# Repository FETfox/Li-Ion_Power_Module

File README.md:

## Status

  **RevA** In development (schematic complete, layout pending)

## Key Components

| Function | IC | Notes |
|----------|----|----|
| Charger | BQ24074 | USB100/500 + ILIM modes |
| Protection | BQ29728 | OCP/OVP/UVP |
| Fuel Gauge | BQ27427 | Coulomb counter |
| Buck-Boost | TPS63020 | ~1.8-5.5V input, 3.3V/5V output |
| MCU (Smart) | ATtiny3217 | CAN interface logic |
| CAN Controller | MCP2515 | SPI interface |
| CAN Transceiver | SN65HVD230 | ISO11898-2 compliant |

## Usage

Battery powered 5w power supply for projects that use 3v3 or 5v.
The smart version tracks system status and communicates over CAN bus.

## Known Issues / TODOs

- [ ] PCB layout and thermal analysis
- [ ] Publish assembly guide and test procedure

## License

CC0

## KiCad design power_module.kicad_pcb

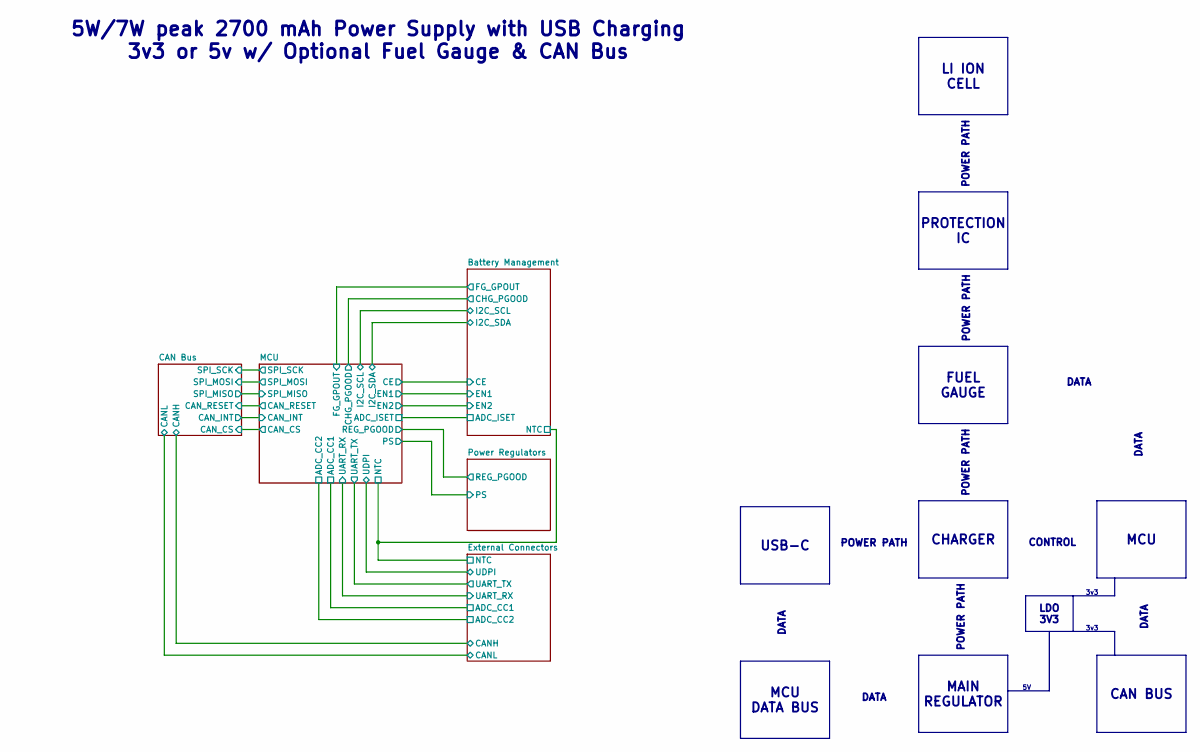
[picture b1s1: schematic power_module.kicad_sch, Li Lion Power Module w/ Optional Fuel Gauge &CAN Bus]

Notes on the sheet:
3v3
5W/7W peak 2700 mAh Power Supply with USB Charging 3v3 or 5v w/ Optional Fuel Gauge & CAN Bus
LDO 3V3
FUEL GAUGE
MCU DATA BUS
DATA
CHARGER
POWER PATH
USB-C
CAN BUS
MAIN REGULATOR
PROTECTION IC
LI ION CELL
MCU
CONTROL

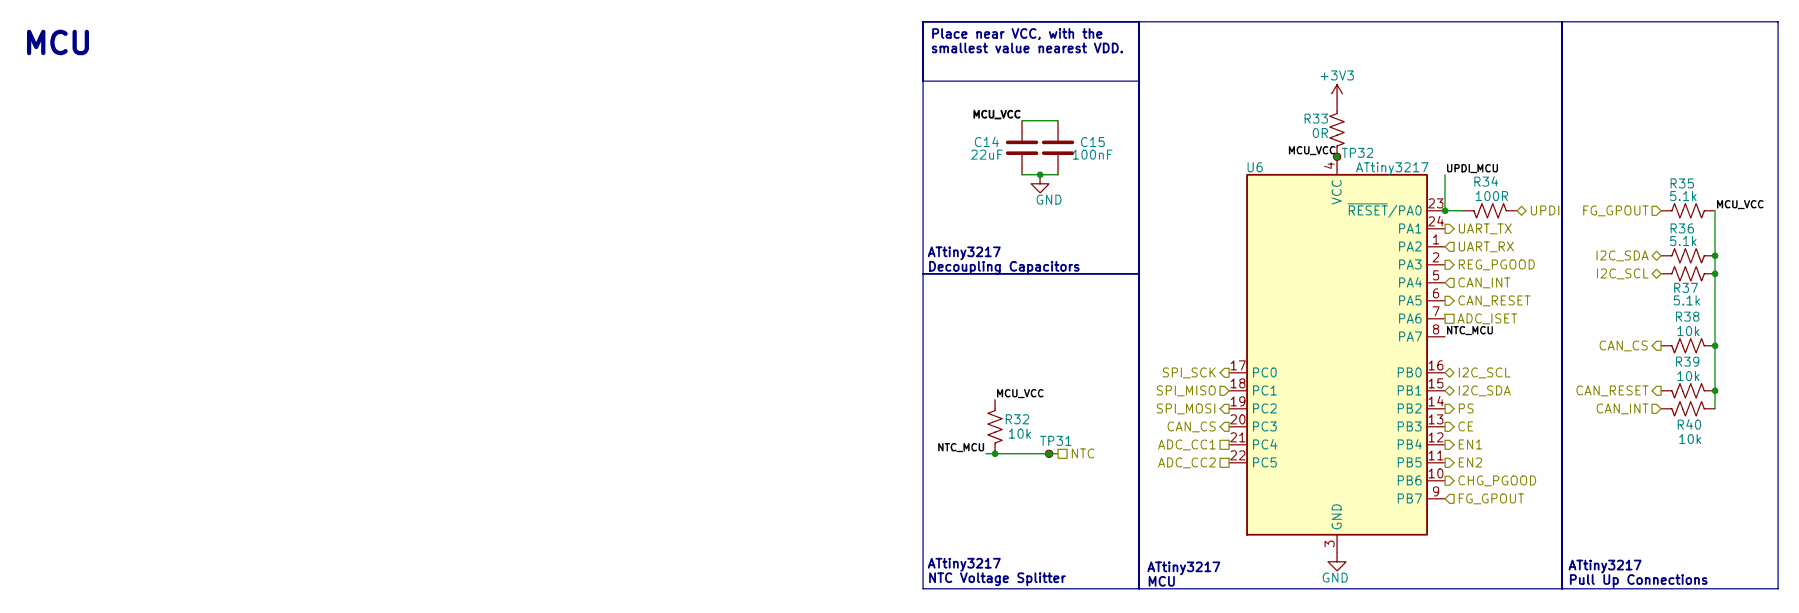
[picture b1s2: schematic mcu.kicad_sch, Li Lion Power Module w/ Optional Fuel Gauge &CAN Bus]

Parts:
C14: 22uF; C_0805_2012Metric; LCSC# C77074
C15: 100nF; C_0603_1608Metric; LCSC# C14663
R32, R38, R39, R40: 10k; R_0603_1608Metric; MFR# RC0603FR-0710KL; LCSC# C98220
R33: 0R; R_0805_2012Metric; LCSC# C54921246
R34: 100R; R_0603_1608Metric; MFR# RC0603FR-07100RL; LCSC# C105588
R35, R36, R37: 5.1k; R_0603_1608Metric; MFR# RC0603FR-075K1L; LCSC# C105580
TP31: NTC; TestPoint_Pad_D1.0mm
TP32: MCU_VCC; TestPoint_Pad_D1.0mm
U6: ATtiny3217; QFN-24-1EP_4x4mm_P0.5mm_EP2.6x2.6mm; LCSC# C15193

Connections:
+3V3: R33.1; also elsewhere on the board
/Battery Management/ADC_ISET: U6.7 (PA6); also elsewhere on the board
/Battery Management/CE: U6.13 (PB3); also elsewhere on the board
/Battery Management/CHG_EN1: U6.12 (PB4); also elsewhere on the board
/Battery Management/CHG_EN2: U6.11 (PB5); also elsewhere on the board
/Battery Management/CHG_PGOOD: U6.10 (PB6); also elsewhere on the board
/Battery Management/FG_GPOUT: R35.1, U6.9 (PB7); also elsewhere on the board
/Battery Management/I2C_SCL: R37.2, U6.16 (PB0); also elsewhere on the board
/Battery Management/I2C_SDA: R36.1, U6.15 (PB1); also elsewhere on the board
/CAN Bus/CAN_CS: R38.2, U6.20 (PC3); also elsewhere on the board
/CAN Bus/CAN_INT: R40.1, U6.5 (PA4); also elsewhere on the board
/CAN Bus/CAN_RESET: R39.2, U6.6 (PA5); also elsewhere on the board
/CAN Bus/SPI_MISO: U6.18 (PC1); also elsewhere on the board
/CAN Bus/SPI_MOSI: U6.19 (PC2); also elsewhere on the board
/CAN Bus/SPI_SCK: U6.17 (PC0); also elsewhere on the board
/External Connectors/ADC_CC1: U6.21 (PC4); also elsewhere on the board
/External Connectors/ADC_CC2: U6.22 (PC5); also elsewhere on the board
/External Connectors/UART_RX: U6.1 (PA2); also elsewhere on the board
/External Connectors/UART_TX: U6.24 (PA1); also elsewhere on the board
/MCU/MCU_VCC: C14.2, C15.2, R32.2, R33.2, R35.2, R36.2, R37.1, R38.1, R39.1, R40.2, TP32.1 (1_1), U6.4 (VCC)
/MCU/NTC_MCU: R32.1, TP31.1 (1_1), U6.8 (PA7); also elsewhere on the board
/MCU/PS: U6.14 (PB2); also elsewhere on the board
/MCU/UPDI: R34.2
/MCU/UPDI_MCU: R34.1, U6.23 (~RESET/PA0)
/Power Regulators/REG_PGOOD: U6.2 (PA3); also elsewhere on the board
GND: C14.1, C15.1, U6.3 (GND), U6.25 (GND); also elsewhere on the board

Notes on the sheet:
ATtiny3217 Pull Up Connections
ATtiny3217 MCU
MCU
ATtiny3217 NTC Voltage Splitter
ATtiny3217 Decoupling Capacitors
Place near VCC, with the smallest value nearest VDD.

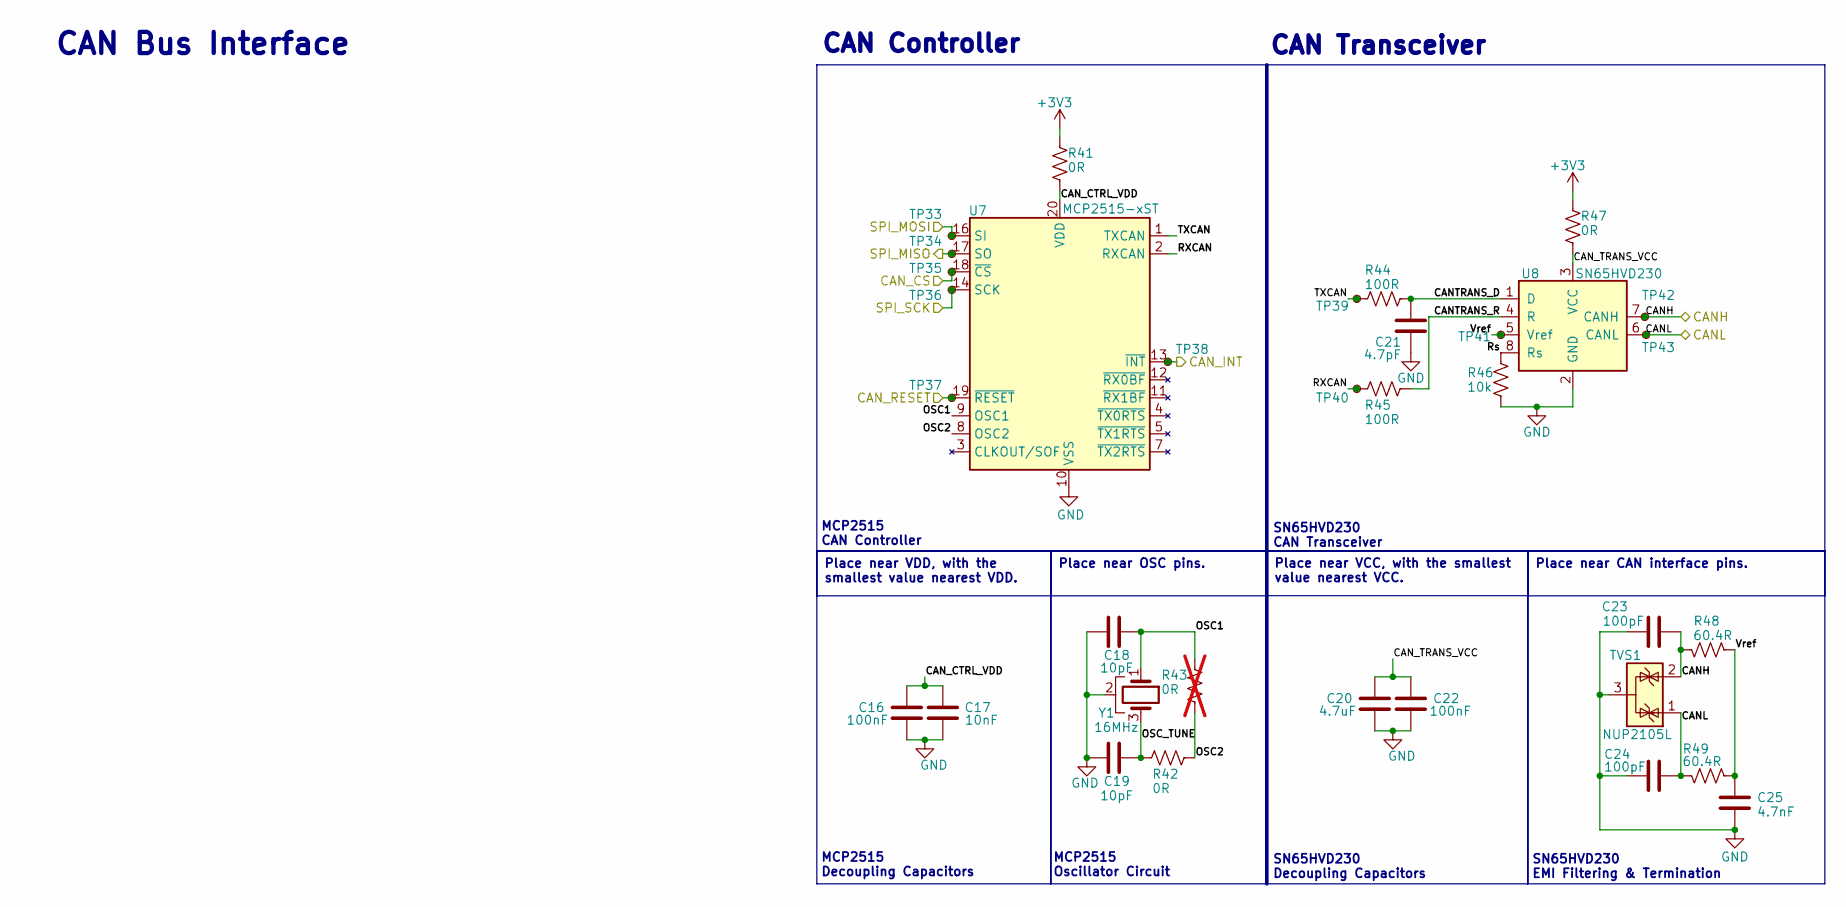
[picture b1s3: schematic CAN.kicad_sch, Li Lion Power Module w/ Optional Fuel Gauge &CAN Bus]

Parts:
C16, C22: 100nF; C_0603_1608Metric; LCSC# C14663
C17: 10nF; C_0603_1608Metric; LCSC# C100042
C18, C19: 10pF; C_0603_1608Metric; LCSC# C106245
C20: 4.7uF; C_0805_2012Metric; LCSC# C96454
C21: 4.7pF; C_0603_1608Metric; LCSC# C1669
C23, C24: 100pF; C_0603_1608Metric; LCSC# C14858
C25: 4.7nF; C_0603_1608Metric; LCSC# C16194364
R41, R42, R47: 0R; R_0805_2012Metric; LCSC# C54921246
R43: 0R; R_0805_2012Metric; LCSC# C54921246; not fitted
R44, R45: 100R; R_0603_1608Metric; LCSC# C105588
R46: 10k; R_0603_1608Metric; LCSC# C98220
R48, R49: 60.4R; R_0603_1608Metric; LCSC# C245987
TP33: SPI_MOSI; TestPoint_Pad_D1.0mm
TP34: SPI_MISO; TestPoint_Pad_D1.0mm
TP35: CAN_CS; TestPoint_Pad_D1.0mm
TP36: SPI_SCK; TestPoint_Pad_D1.0mm
TP37: CAN_RESET; TestPoint_Pad_D1.0mm
TP38: CAN_INT; TestPoint_Pad_D1.0mm
TP39: TXCAN; TestPoint_Pad_D1.0mm
TP40: RXCAN; TestPoint_Pad_D1.0mm
TP41: VREF; TestPoint_Pad_D1.0mm
TP42: CANH; TestPoint_Pad_D1.0mm
TP43: CANL; TestPoint_Pad_D1.0mm
TVS1: NUP2105L; SOT-23; MFR# NUP2105LT1G; LCSC# C14486
U7: MCP2515-xST; TSSOP-20_4.4x6.5mm_P0.65mm; LCSC# C15193
U8: SN65HVD230; SOIC-8_3.9x4.9mm_P1.27mm; LCSC# C12084
Y1: 16MHz; Crystal_SMD_3225-4Pin_3.2x2.5mm; MFR# X322516MLB4SI; LCSC# C13738

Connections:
+3V3: R41.1, R47.1; also elsewhere on the board
/CAN Bus/CANH: C23.2, R48.2, TP42.1 (1_1), TVS1.2 (K), U8.7 (CANH); also elsewhere on the board
/CAN Bus/CANL: C24.1, R49.1, TP43.1 (1_1), TVS1.1 (K), U8.6 (CANL); also elsewhere on the board
/CAN Bus/CANTRANS_D: C21.1, R44.2, U8.1 (D)
/CAN Bus/CANTRANS_R: R45.1, U8.4 (R)
/CAN Bus/CAN_CS: TP35.1 (1_1), U7.18 (~CS); also elsewhere on the board
/CAN Bus/CAN_CTRL_VDD: C16.2, C17.2, R41.2, U7.20 (VDD)
/CAN Bus/CAN_INT: TP38.1 (1_1), U7.13 (~INT); also elsewhere on the board
/CAN Bus/CAN_RESET: TP37.1 (1_1), U7.19 (~RESET); also elsewhere on the board
/CAN Bus/CAN_TRANS_VCC: C20.2, C22.2, R47.2, U8.3 (VCC)
/CAN Bus/OSC1: C18.2, R43.1, U7.9 (OSC1), Y1.1
/CAN Bus/OSC2: R42.2, R43.2, U7.8 (OSC2)
/CAN Bus/OSC_TUNE: C19.2, R42.1, Y1.3
/CAN Bus/RXCAN: R45.2, TP40.1 (1_1), U7.2 (RXCAN)
/CAN Bus/Rs: R46.2, U8.8 (Rs)
/CAN Bus/SPI_MISO: TP34.1 (1_1), U7.17 (SO); also elsewhere on the board
/CAN Bus/SPI_MOSI: TP33.1 (1_1), U7.16 (SI); also elsewhere on the board
/CAN Bus/SPI_SCK: TP36.1 (1_1), U7.14 (SCK); also elsewhere on the board
/CAN Bus/TXCAN: R44.1, TP39.1 (1_1), U7.1 (TXCAN)
/CAN Bus/Vref: C25.1, R48.1, R49.2, TP41.1 (1_1), U8.5 (Vref)
GND: C16.1, C17.1, C18.1, C19.1, C20.1, C21.2, C22.1, C23.1, C24.2, C25.2, R46.1, TVS1.3 (A), U7.10 (VSS), U8.2 (GND), Y1.2 (GND), Y1.4 (GND); also elsewhere on the board

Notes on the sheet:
CAN Transceiver
CAN Bus Interface
SN65HVD230 EMI Filtering & Termination
CAN Controller
MCP2515 Oscillator Circuit
SN65HVD230 CAN Transceiver
SN65HVD230 Decoupling Capacitors
MCP2515 Decoupling Capacitors
MCP2515 CAN Controller
Place near CAN interface pins.
Place near OSC pins.
Place near VCC, with the smallest value nearest VCC.
Place near VDD, with the smallest value nearest VDD.

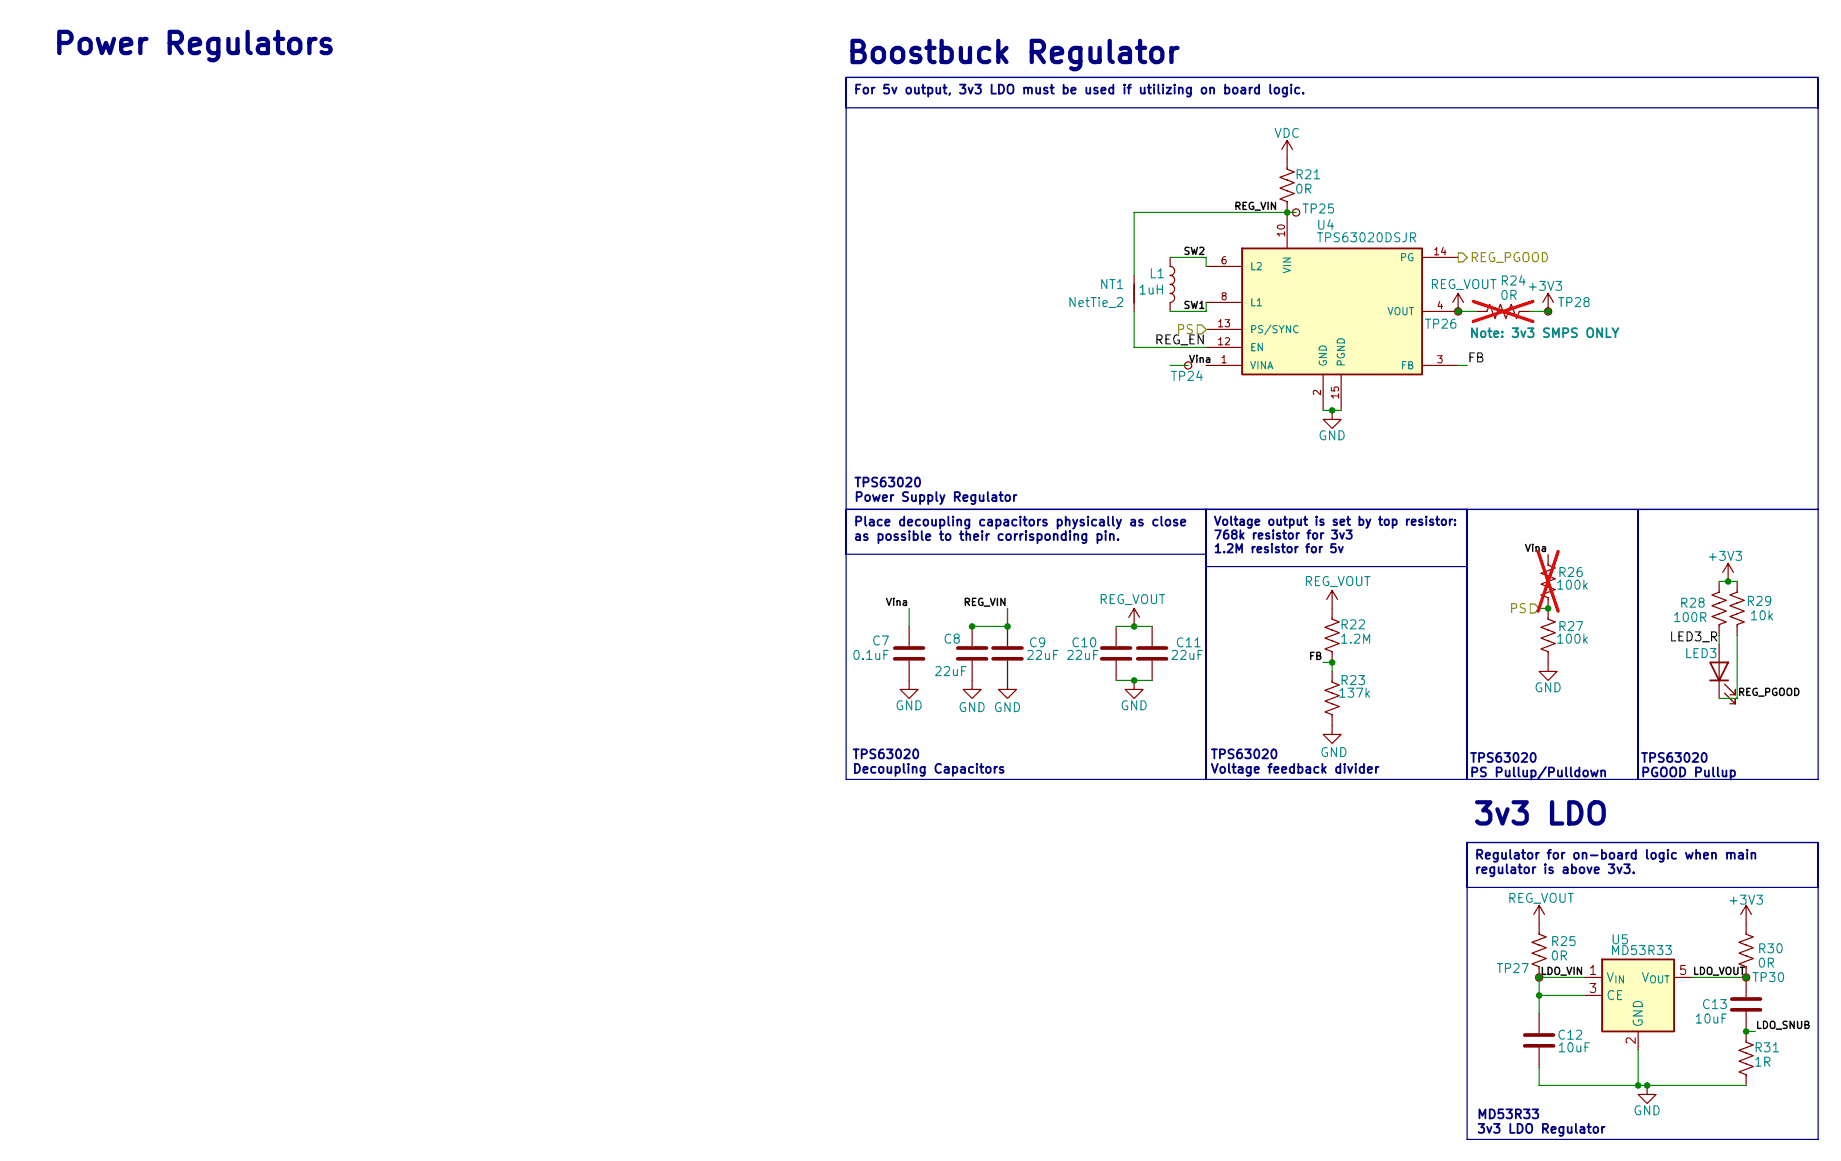
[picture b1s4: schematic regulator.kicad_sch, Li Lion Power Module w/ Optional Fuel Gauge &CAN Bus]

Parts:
C7: 0.1uF; C_0603_1608Metric; LCSC# C14663
C8, C9, C10, C11: 22uF; C_0805_2012Metric; LCSC# C77074
C12, C13: 10uF; C_0603_1608Metric; LCSC# C90053
L1: 1uH; DR73; MFR# DR73-1R0-R; LCSC# C2454006
LED3: PGOOD; LED_0603_1608Metric; LCSC# C2286
NT1: NetTie_2; NetTie-2_SMD_Pad2.0mm
R21: 0R; R_1206_3216Metric; MFR# HP06W2J0000T5E; LCSC# C473612
R22: 1.2M; R_0603_1608Metric; MFR# RC0603FR-071M2L; LCSC# C137774
R23: 137k; R_0603_1608Metric; MFR# RC0603FR-07137KL; LCSC# C137797
R24: 0R; R_1206_3216Metric; MFR# HP06W2J0000T5E; LCSC# C473612; not fitted
R25, R30: 0R; R_0805_2012Metric; LCSC# C54921246
R26: 100k; R_0603_1608Metric; MFR# RC0603FR-07100KL; LCSC# C14675; not fitted
R27: 100k; R_0603_1608Metric; MFR# RC0603FR-07100KL; LCSC# C14675
R28: 100R; R_0603_1608Metric; MFR# RC0603FR-07100RL; LCSC# C105588
R29: 10k; R_0603_1608Metric; MFR# RC0603FR-0710KL; LCSC# C98220
R31: 1R; R_0603_1608Metric; MFR# RC0603FR-071RL; LCSC# C112305
TP24: REG_Vina; TestPoint_Pad_D1.0mm
TP25: REG_VIN; TestPoint_Pad_D1.0mm
TP26: REG_OUT; TestPoint_Pad_D1.0mm
TP27: LDO_VIN; TestPoint_Pad_D1.0mm
TP28: +3v3; TestPoint_Pad_D1.0mm
TP30: LDO_VOUT; TestPoint_Pad_D1.0mm
U4: TPS63020DSJR; IC_TPS63020DSJR; MFR# TPS63020DSJR; LCSC# C15483
U5: MD53R33; SOT-23-5; MFR# MD53R33; LCSC# C111685

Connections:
+3V3: R24.2, R28.2, R29.2, R30.2, TP28.1 (1_1); also elsewhere on the board
/MCU/PS: R26.2, R27.1, U4.13 (PS/SYNC); also elsewhere on the board
/Power Regulators/FB: R22.2, R23.1, U4.3 (FB)
/Power Regulators/LDO_SNUB: C13.2, R31.1
/Power Regulators/LDO_VIN: C12.1, R25.1, TP27.1 (1_1), U5.1 (V_{IN}), U5.3 (CE)
/Power Regulators/LDO_VOUT: C13.1, R30.1, TP30.1 (1_1), U5.5 (V_{OUT})
/Power Regulators/LED3_R: LED3.2 (A), R28.1
/Power Regulators/REG_EN: NT1.1, U4.12 (EN)
/Power Regulators/REG_PGOOD: LED3.1 (K), R29.1, U4.14 (PG); also elsewhere on the board
/Power Regulators/REG_VIN: C8.1, C9.1, NT1.2, R21.2, TP25.1 (1_1), U4.10 (VIN), U4.11 (VIN)
/Power Regulators/SW1: L1.2, U4.8 (L1), U4.9 (L1)
/Power Regulators/SW2: L1.1, U4.6 (L2), U4.7 (L2)
/Power Regulators/Vina: C7.1, R26.1, TP24.1 (1_1)
GND: C7.2, C8.2, C9.2, C10.2, C11.2, C12.2, R23.2, R27.2, R31.2, U4.2 (GND), U4.15 (PGND), U5.2 (GND); also elsewhere on the board
REG_VOUT: C10.1, C11.1, R22.1, R24.1, R25.2, TP26.1 (1_1), U4.4 (VOUT), U4.5 (VOUT); also elsewhere on the board
VDC: R21.1; also elsewhere on the board

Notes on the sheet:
Power Regulators
3v3 LDO
Boostbuck Regulator
TPS63020 Decoupling Capacitors
MD53R33 3v3 LDO Regulator
TPS63020 Voltage feedback divider
TPS63020 PS Pullup/Pulldown
TPS63020 PGOOD Pullup
TPS63020 Power Supply Regulator
Place decoupling capacitors physically as close as possible to their corrisponding pin.
For 5v output, 3v3 LDO must be used if utilizing on board logic.
Voltage output is set by top resistor: 768k resistor for 3v3 1.2M resistor for 5v
Regulator for on-board logic when main regulator is above 3v3.

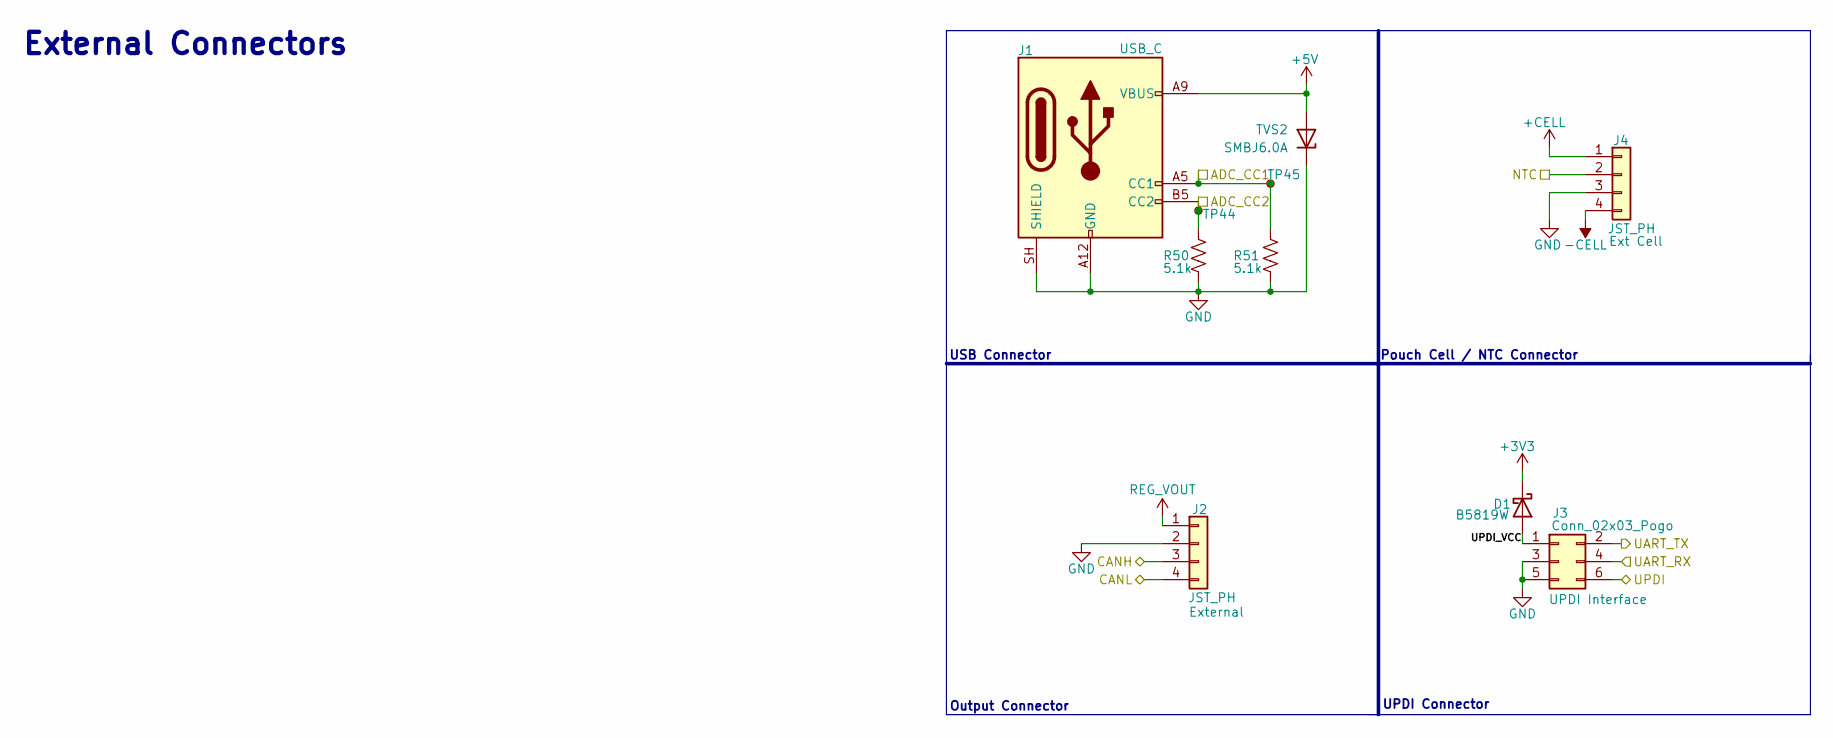
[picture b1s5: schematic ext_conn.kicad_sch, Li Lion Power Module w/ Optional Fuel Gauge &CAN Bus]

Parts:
D1: B5819W; D_SOD-123; LCSC# C64885
J1: USB_C; USB_C_Receptacle_GCT_USB4125-xx-x-0190_6P_TopMnt_Horizontal
J2, J4: JST_PH; JST_PH_B4B-PH-K_1x04_P2.00mm_Vertical
J3: Conn_02x03_Pogo; PinSocket_2x03_P2.54mm_Vertical
R50, R51: 5.1k; R_0603_1608Metric; MFR# RC0603FR-075K1L; LCSC# C105580
TP44: ADC_CC2; TestPoint_Pad_D1.0mm
TP45: ADC_CC1; TestPoint_Pad_D1.0mm
TVS2: SMBJ6.0A; D_SMB; MFR# SMBJ6.0A; LCSC# C140903

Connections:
+3V3: D1.1 (K); also elsewhere on the board
+5V: J1.A9 (VBUS), J1.B9 (VBUS), TVS2.2 (A); also elsewhere on the board
+CELL: J4.1; also elsewhere on the board
-CELL: J4.4; also elsewhere on the board
/CAN Bus/CANH: J2.3; also elsewhere on the board
/CAN Bus/CANL: J2.4; also elsewhere on the board
/External Connectors/ADC_CC1: J1.A5 (CC1), R51.2, TP45.1 (1_1); also elsewhere on the board
/External Connectors/ADC_CC2: J1.B5 (CC2), R50.2, TP44.1 (1_1); also elsewhere on the board
/External Connectors/UART_RX: J3.4; also elsewhere on the board
/External Connectors/UART_TX: J3.2; also elsewhere on the board
/External Connectors/UPDI: J3.6
/External Connectors/UPDI_VCC: D1.2 (A), J3.1
/MCU/NTC_MCU: J4.2; also elsewhere on the board
GND: J1.A12 (GND), J1.B12 (GND), J1.SH (SHIELD), J2.2, J3.3, J3.5, J4.3, R50.1, R51.1, TVS2.1 (K); also elsewhere on the board
REG_VOUT: J2.1; also elsewhere on the board

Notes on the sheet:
Pouch Cell / NTC Connector
USB Connector
External Connectors
UPDI Connector
Output Connector

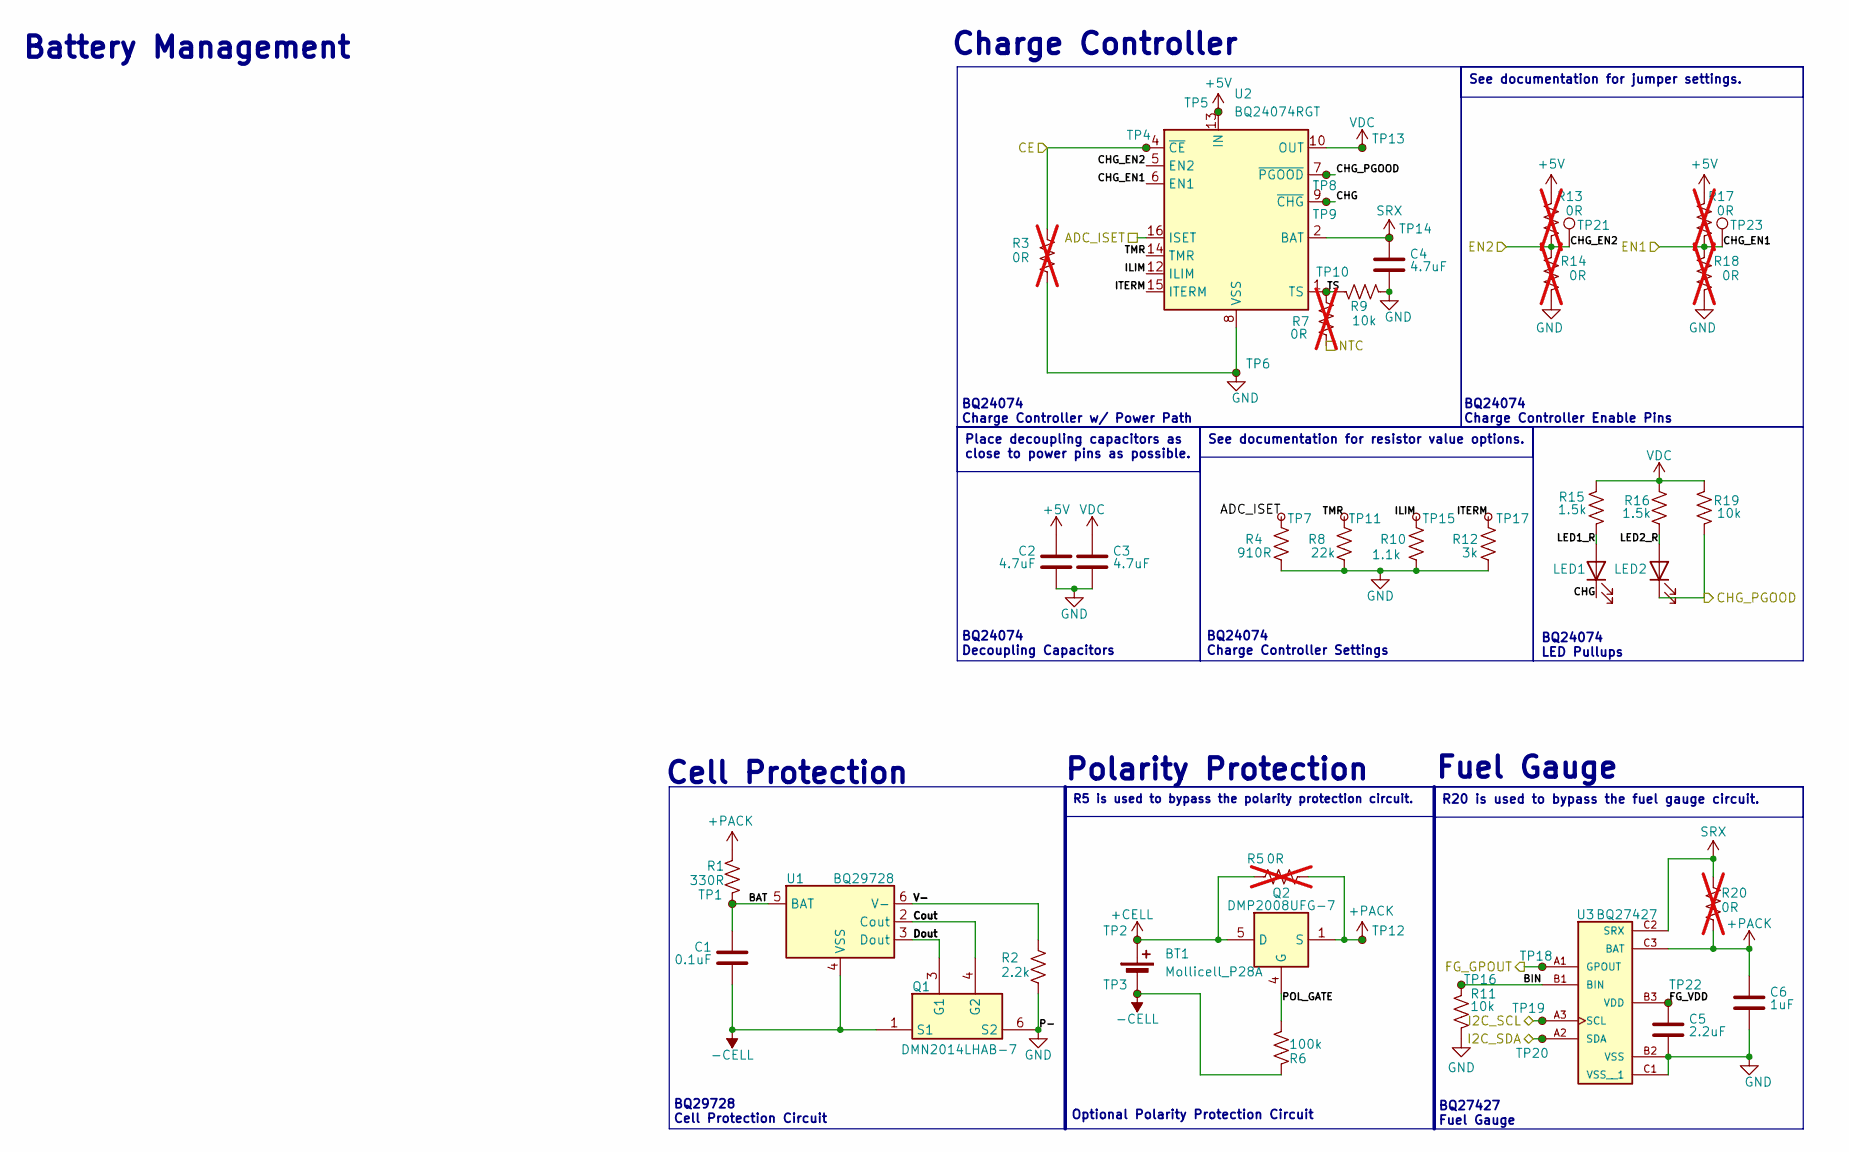
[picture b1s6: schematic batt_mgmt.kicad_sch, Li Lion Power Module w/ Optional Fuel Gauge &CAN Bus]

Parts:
BT1: Mollicell_P28A; BatteryHolder_HAN_BH-18650-1
C1: 0.1uF; C_0603_1608Metric; LCSC# C14663
C2, C3, C4: 4.7uF; C_0805_2012Metric; LCSC# C96454
C5: 2.2uF; C_0805_2012Metric; LCSC# C1607
C6: 1uF; C_0603_1608Metric; LCSC# C26413
LED1: CHG; LED_0603_1608Metric; LCSC# C2286
LED2: CHG_PGOOD; LED_0603_1608Metric; LCSC# C2286
Q1: DMN2014LHAB-7; U-DFN2030-6; Mouser Part Number 621-DMN2014LHAB-7
Q2: DMP2008UFG-7; Diodes_PowerDI3333-8; Mouser Part Number 621-DMP2008UFG-7
R1: 330R; R_0603_1608Metric; LCSC# C105881
R2: 2.2k; R_0603_1608Metric; LCSC# C114662
R3, R7, R13, R14, R17, R18: 0R; R_0805_2012Metric; LCSC# C54921246; not fitted
R4: 910R; R_0603_1608Metric; LCSC# C185304
R5, R20: 0R; R_1206_3216Metric; MFR# HP06W2J0000T5E; LCSC# C473612; not fitted
R6: 100k; R_0603_1608Metric; LCSC# C14675
R8: 22k; R_0603_1608Metric; LCSC# C114065
R9: 10k; R_0603_1608Metric; MFR# RC0603FR-0710KL; LCSC# C98220
R10: 1.1k; R_0603_1608Metric; LCSC# C137780
R11, R19: 10k; R_0603_1608Metric; LCSC# C98220
R12: 3k; R_0603_1608Metric; LCSC# C126358
R15, R16: 1.5k; R_0603_1608Metric; LCSC# C114680
TP1: BAT; TestPoint_Pad_D1.0mm
TP2: +Cell; TestPoint_Pad_D1.0mm
TP3: -Cell; TestPoint_Pad_D1.0mm
TP4: CE; TestPoint_Pad_D1.0mm
TP5: 5V; TestPoint_Pad_D1.0mm
TP6: GND; TestPoint_Pad_D1.0mm
TP7: ADC_ISET; TestPoint_Pad_D1.0mm
TP8: CHG_PGOOD; TestPoint_Pad_D1.0mm
TP9: CHG; TestPoint_Pad_D1.0mm
TP10: TS; TestPoint_Pad_D1.0mm
TP11: TMR; TestPoint_Pad_D1.0mm
TP12: +Pack; TestPoint_Pad_D1.0mm
TP13: CHG_OUT; TestPoint_Pad_D1.0mm
TP14: SRX; TestPoint_Pad_D1.0mm
TP15: ILIM; TestPoint_Pad_D1.0mm
TP16: BIN; TestPoint_Pad_D1.0mm
TP17: ITERM; TestPoint_Pad_D1.0mm
TP18: FG_GPOUT; TestPoint_Pad_D1.0mm
TP19: I2C_SCL; TestPoint_Pad_D1.0mm
TP20: I2C_SDA; TestPoint_Pad_D1.0mm
TP21: EN2; TestPoint_Pad_D1.0mm
TP22: FG_VDD; TestPoint_Pad_D1.0mm
TP23: EN1; TestPoint_Pad_D1.0mm
U1: BQ29728; WSON-6_1.5x1.5mm_P0.5mm; LCSC# C3682679
U2: BQ24074RGT; VQFN-16-1EP_3x3mm_P0.5mm_EP1.6x1.6mm_ThermalVias; LCSC# C54313
U3: BQ27427; LCSC# C6075475

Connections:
+5V: C2.1, R13.2, R17.2, TP5.1 (1_1), U2.13 (IN); also elsewhere on the board
+CELL: BT1.1 (+), Q2.5 (D), R5.1, TP2.1 (1_1); also elsewhere on the board
+PACK: C6.1, Q2.1 (S), Q2.2 (S), Q2.3 (S), R1.1, R5.2, R20.2, TP12.1 (1_1), U3.C3 (BAT)
-CELL: BT1.2 (-), C1.2, Q1.1 (S1), R6.1, TP3.1 (1_1), U1.4 (VSS); also elsewhere on the board
/Battery Management/ADC_ISET: R4.1, TP7.1 (1_1), U2.16 (ISET); also elsewhere on the board
/Battery Management/BAT: C1.1, R1.2, TP1.1 (1_1), U1.5 (BAT)
/Battery Management/BIN: R11.1, TP16.1 (1_1), U3.B1 (BIN)
/Battery Management/CE: R3.2, TP4.1 (1_1), U2.4 (~CE); also elsewhere on the board
/Battery Management/CHG: LED1.1 (K), TP9.1 (1_1), U2.9 (~CHG)
/Battery Management/CHG_EN1: R17.1, R18.2, TP23.1 (1_1), U2.6 (EN1); also elsewhere on the board
/Battery Management/CHG_EN2: R13.1, R14.2, TP21.1 (1_1), U2.5 (EN2); also elsewhere on the board
/Battery Management/CHG_PGOOD: LED2.1 (K), R19.1, TP8.1 (1_1), U2.7 (~PGOOD); also elsewhere on the board
/Battery Management/Cout: Q1.4 (G2), U1.2 (Cout)
/Battery Management/Dout: Q1.3 (G1), U1.3 (Dout)
/Battery Management/FG_GPOUT: TP18.1 (1_1), U3.A1 (GPOUT); also elsewhere on the board
/Battery Management/FG_VDD: C5.1, TP22.1 (1_1), U3.B3 (VDD)
/Battery Management/I2C_SCL: TP19.1 (1_1), U3.A3 (SCL); also elsewhere on the board
/Battery Management/I2C_SDA: TP20.1 (1_1), U3.A2 (SDA); also elsewhere on the board
/Battery Management/ILIM: R10.1, TP15.1 (1_1), U2.12 (ILIM)
/Battery Management/ITERM: R12.1, TP17.1 (1_1), U2.15 (ITERM)
/Battery Management/LED1_R: LED1.2 (A), R15.1
/Battery Management/LED2_R: LED2.2 (A), R16.1
/Battery Management/POL_GATE: Q2.4 (G), R6.2
/Battery Management/TMR: R8.1, TP11.1 (1_1), U2.14 (TMR)
/Battery Management/TS: R7.2, R9.2, TP10.1 (1_1), U2.1 (TS)
/Battery Management/V-: R2.1, U1.6 (V-)
/MCU/NTC_MCU: R7.1; also elsewhere on the board
GND: C2.2, C3.2, C4.2, C5.2, C6.2, Q1.6 (S2), R2.2, R3.1, R4.2, R8.2, R9.1, R10.2, R11.2, R12.2, R14.1, R18.1, TP6.1 (1_1), U2.8 (VSS), U2.17 (VSS), U3.B2 (VSS), U3.C1 (VSS__1); also elsewhere on the board
SRX: C4.1, R20.1, TP14.1 (1_1), U2.2 (BAT), U2.3 (BAT), U3.C2 (SRX)
VDC: C3.1, R15.2, R16.2, R19.2, TP13.1 (1_1), U2.10 (OUT), U2.11 (OUT); also elsewhere on the board

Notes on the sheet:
Cell Protection
Polarity Protection
BQ27427 Fuel Gauge
Fuel Gauge
Battery Management
BQ29728 Cell Protection Circuit
BQ24074 Decoupling Capacitors
Charge Controller
BQ24074 Charge Controller Settings
Optional Polarity Protection Circuit
BQ24074 LED Pullups
BQ24074 Charge Controller w/ Power Path
BQ24074 Charge Controller Enable Pins
Place decoupling capacitors as close to power pins as possible.
R20 is used to bypass the fuel gauge circuit.
See documentation for jumper settings.
See documentation for resistor value options.
R5 is used to bypass the polarity protection circuit.

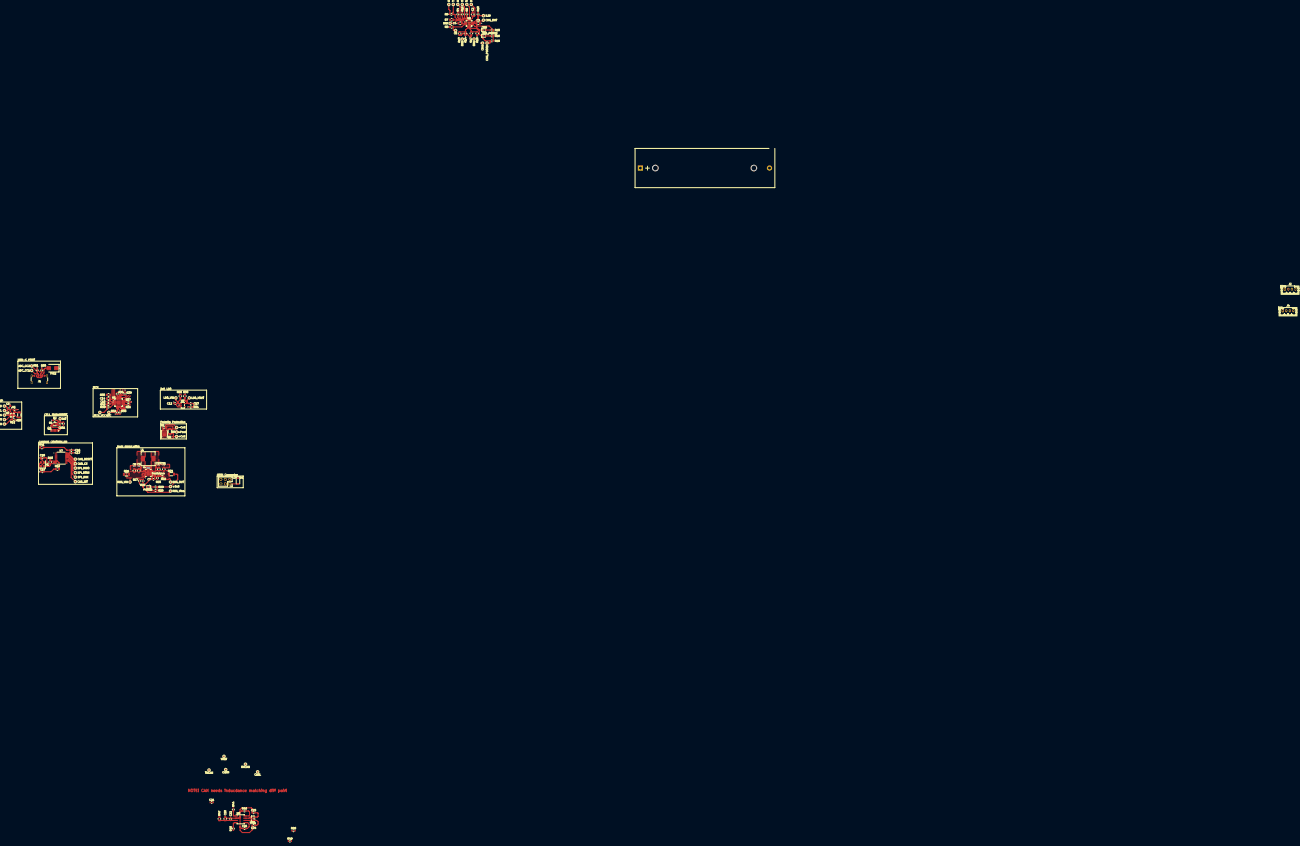
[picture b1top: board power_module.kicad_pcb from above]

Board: 4 copper layers, 144 parts (0 on the bottom side), 70 nets.

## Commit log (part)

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2026-06-22 Add gitignore
2026-06-22 Initial commit - project-local libraries
2026-06-22 clean up
2026-06-22 Add ReadMe
2026-06-25 Added Graph & cleaned up title and layout
